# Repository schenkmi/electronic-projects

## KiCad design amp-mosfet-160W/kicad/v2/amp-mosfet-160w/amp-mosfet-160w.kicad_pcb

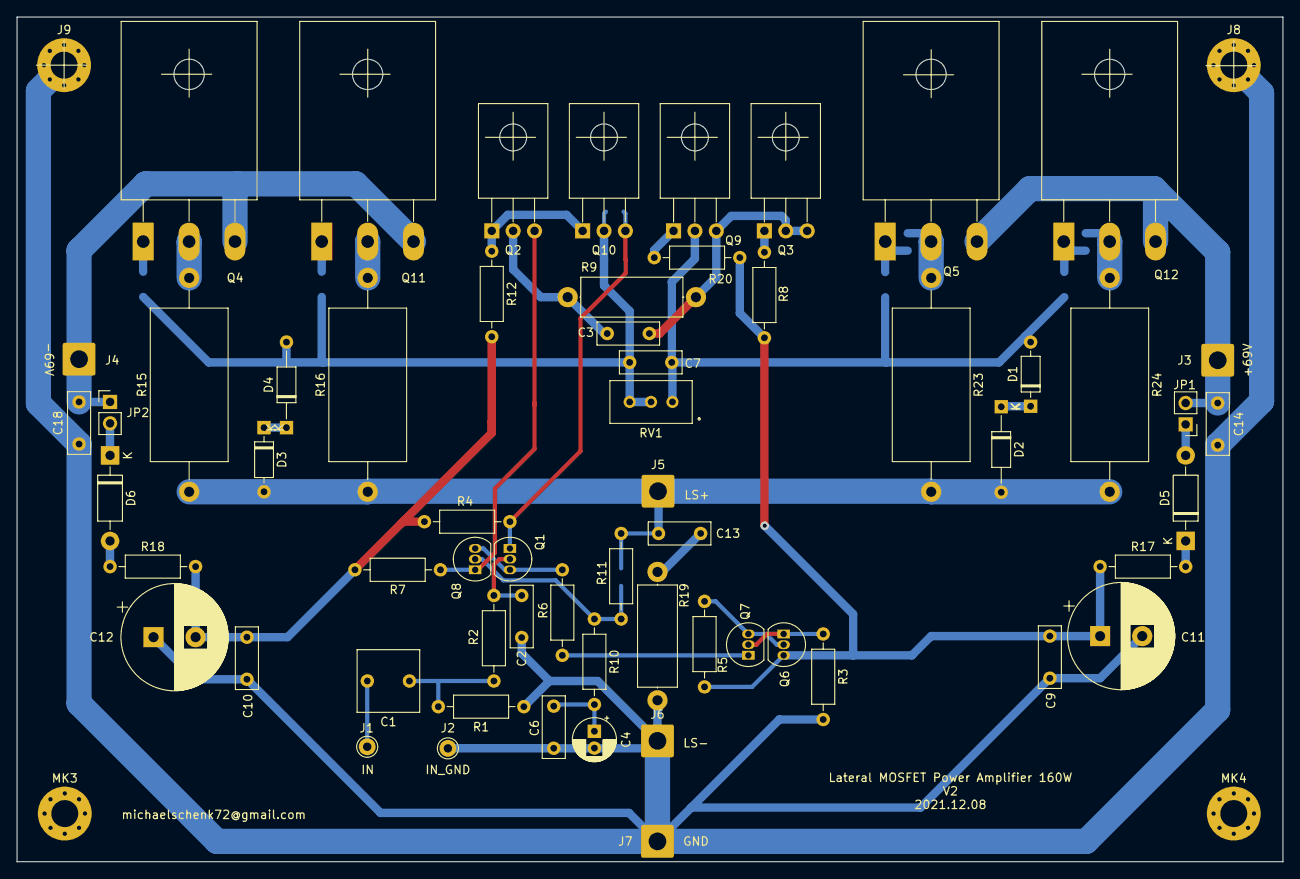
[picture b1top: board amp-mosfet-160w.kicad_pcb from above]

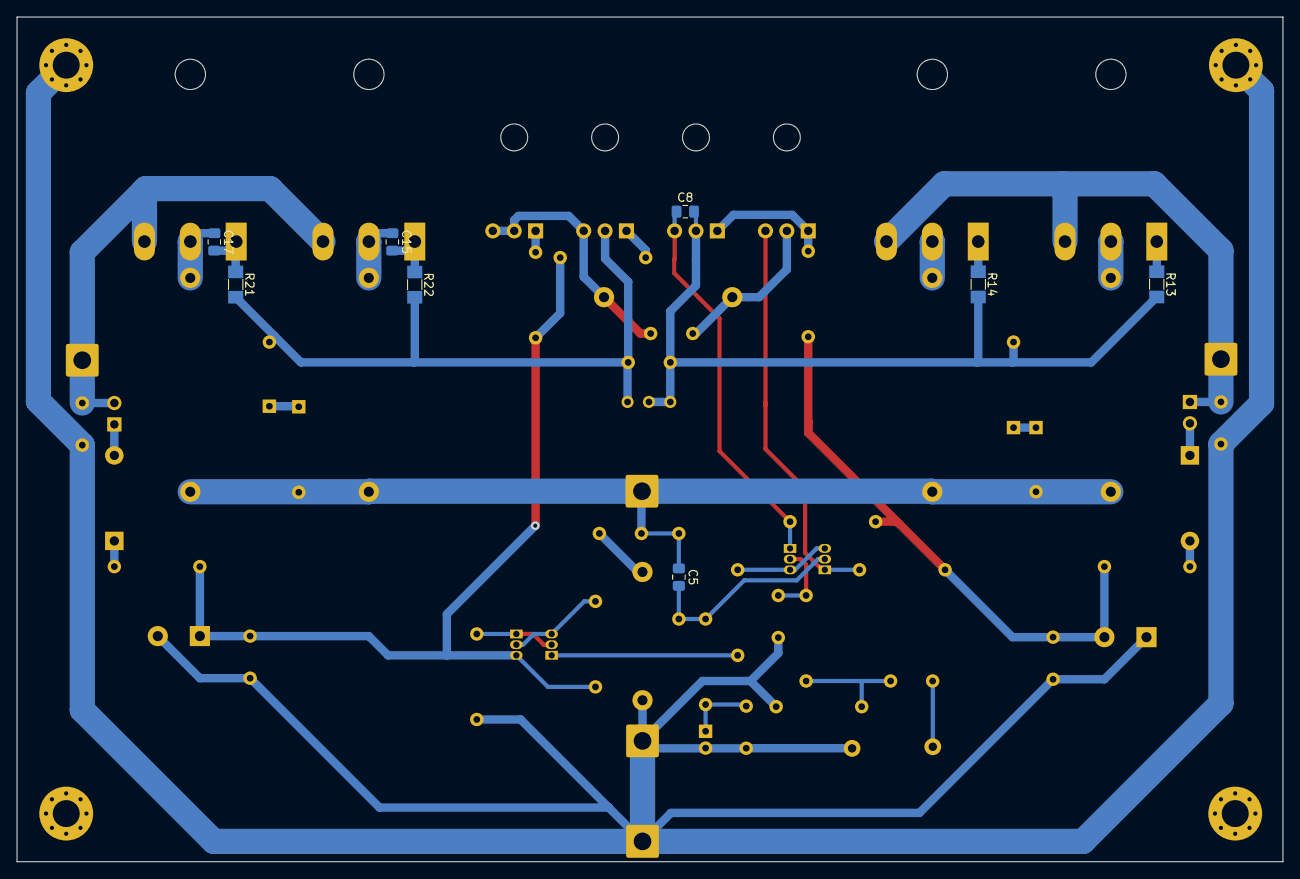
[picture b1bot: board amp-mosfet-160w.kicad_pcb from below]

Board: 2 copper layers, 150.4 x 100.3 mm, 73 parts (8 on the bottom side), 39 nets.

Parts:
C1: 2.2uF; C_Rect_L7.2mm_W7.2mm_P5.00mm_FKS2_FKP2_MKS2_MKP2
C2: 1n; C_Rect_L7.2mm_W2.5mm_P5.00mm_FKS2_FKP2_MKS2_MKP2
C3: 10n; C_Rect_L7.2mm_W2.5mm_P5.00mm_FKS2_FKP2_MKS2_MKP2
C4: 47u/16V; CP_Radial_D5.0mm_P2.00mm
C5: 10p; C_0805_2012Metric_Pad1.18x1.45mm_HandSolder
C6, C7, C9, C10, C14, C18: 100n; C_Rect_L7.2mm_W2.5mm_P5.00mm_FKS2_FKP2_MKS2_MKP2
C8: 18p; C_0805_2012Metric_Pad1.18x1.45mm_HandSolder
C11, C12: 220u/100V; CP_Radial_D12.5mm_P5.00mm
C13: 22n; C_Rect_L7.2mm_W2.5mm_P5.00mm_FKS2_FKP2_MKS2_MKP2
C15: 330p; C_0805_2012Metric_Pad1.18x1.45mm_HandSolder
C17: 470p; C_0805_2012Metric_Pad1.18x1.45mm_HandSolder
D1, D3: 1N914; D_DO-35_SOD27_P7.62mm_Horizontal
D2, D4: 12V/0.5W; D_DO-35_SOD27_P10.16mm_Horizontal
D5, D6: 1N4002; D_DO-41_SOD81_P10.16mm_Horizontal
J1, J2: Conn_01x01; Pin_D1.0mm_L10.0mm
J3: +69V; SolderWire-1.5sqmm_1x01_D1.7mm_OD3.9mm
J4: -69V; SolderWire-1.5sqmm_1x01_D1.7mm_OD3.9mm
J5: LS+; SolderWire-1.5sqmm_1x01_D1.7mm_OD3.9mm
J6: LS-; SolderWire-1.5sqmm_1x01_D1.7mm_OD3.9mm
J7: GND; SolderWire-1.5sqmm_1x01_D1.7mm_OD3.9mm
J8, J9: GND; MountingHole_3.2mm_M3_Pad_Via
JP1, JP2: Jump; PinHeader_1x02_P2.54mm_Vertical
MK3, MK4: Mounting_Hole_PAD; MountingHole_3.2mm_M3_Pad_Via
Q1, Q6, Q7, Q8: BC556; TO-92_Inline
Q2, Q10: MJE340; TO-126-3_Horizontal_TabDown
Q3, Q9: MJE350; TO-126-3_Horizontal_TabDown
Q4, Q11: ECX10P20; TO-247-3_Horizontal_TabDown
Q5, Q12: ECX10N20; TO-247-3_Horizontal_TabDown
R1, R11: 33k; R_Axial_DIN0207_L6.3mm_D2.5mm_P10.16mm_Horizontal
R2, R10: 1k; R_Axial_DIN0207_L6.3mm_D2.5mm_P10.16mm_Horizontal
R3, R6: 22k; R_Axial_DIN0207_L6.3mm_D2.5mm_P10.16mm_Horizontal
R4, R7: 4k7; R_Axial_DIN0207_L6.3mm_D2.5mm_P10.16mm_Horizontal
R5: 680R; R_Axial_DIN0207_L6.3mm_D2.5mm_P10.16mm_Horizontal
R8, R12, R17, R18, R20: 100R; R_Axial_DIN0207_L6.3mm_D2.5mm_P10.16mm_Horizontal
R9: 12k/1W; R_Axial_DIN0414_L11.9mm_D4.5mm_P15.24mm_Horizontal
R13, R14, R21, R22: 220R; R_MiniMELF_MMA-0204
R15, R16, R23, R24: 0.22R; R_Axial_DIN0918_L18.0mm_D9.0mm_P25.40mm_Horizontal
R19: 6.8R/1W; R_Axial_DIN0414_L11.9mm_D4.5mm_P15.24mm_Horizontal
RV1: 200R; Potentiometer_Bourns_3296W_Vertical

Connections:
GND: C2.2, C4.2, C6.2, C9.2, C10.1, C11.2, C12.1, C14.2, C18.1, J2.1, J6.1, J7.1, J8.1, J9.1, R1.2, R3.2, R19.2
unnamed: C1.1, R1.1, R2.2
unnamed: C1.2, J1.1
unnamed: C2.1, Q1.2, R2.1
unnamed: C3.1, Q3.2, Q3.3, Q9.3, R9.1
unnamed: C3.2, Q2.2, R9.2
unnamed: C4.1, C6.1, R10.2
unnamed: C5.2, Q8.2, R10.1, R11.2
unnamed: C7.1, C8.2, D4.2, Q10.2, R13.2, R14.2, RV1.2, RV1.3
unnamed: C7.2, D1.2, Q9.2, R21.2, R22.2, RV1.1
unnamed: C8.1, Q1.1, Q10.3, R4.1
unnamed: C10.2, C12.2, R4.2, R7.2, R12.2, R18.2
unnamed: C9.1, C11.1, Q6.3, R5.1, R8.1, R17.1, R20.1
unnamed: C5.1, C13.1, D2.2, D3.2, J5.1, R11.1, R15.1, R16.1, R23.2, R24.2
unnamed: C13.2, R19.1
unnamed: C14.1, J3.1, JP1.2, Q5.3, Q12.3
unnamed: C15.1, Q5.2, R23.1
unnamed: C15.2, Q5.1, R22.1
unnamed: C17.1, Q12.2, R24.1
unnamed: C17.2, Q12.1, R21.1
unnamed: C18.2, J4.1, JP2.1, Q4.3, Q11.3
unnamed: D1.1, D2.1
unnamed: D3.1, D4.1
unnamed: D5.1, R17.2
unnamed: D5.2, JP1.1
unnamed: D6.1, JP2.2
unnamed: D6.2, R18.1
unnamed: Q1.3, Q8.3, R6.2
unnamed: Q2.3, Q8.1, R7.1
unnamed: Q3.1, R8.2
unnamed: Q4.1, R13.1
unnamed: Q4.2, R15.2
unnamed: Q6.1, Q7.2, R3.1
unnamed: Q6.2, Q7.3, R5.2
unnamed: Q7.1, R6.1
unnamed: Q9.1, R20.2
unnamed: Q2.1, Q10.1, R12.1
unnamed: Q11.1, R14.1
unnamed: Q11.2, R16.2

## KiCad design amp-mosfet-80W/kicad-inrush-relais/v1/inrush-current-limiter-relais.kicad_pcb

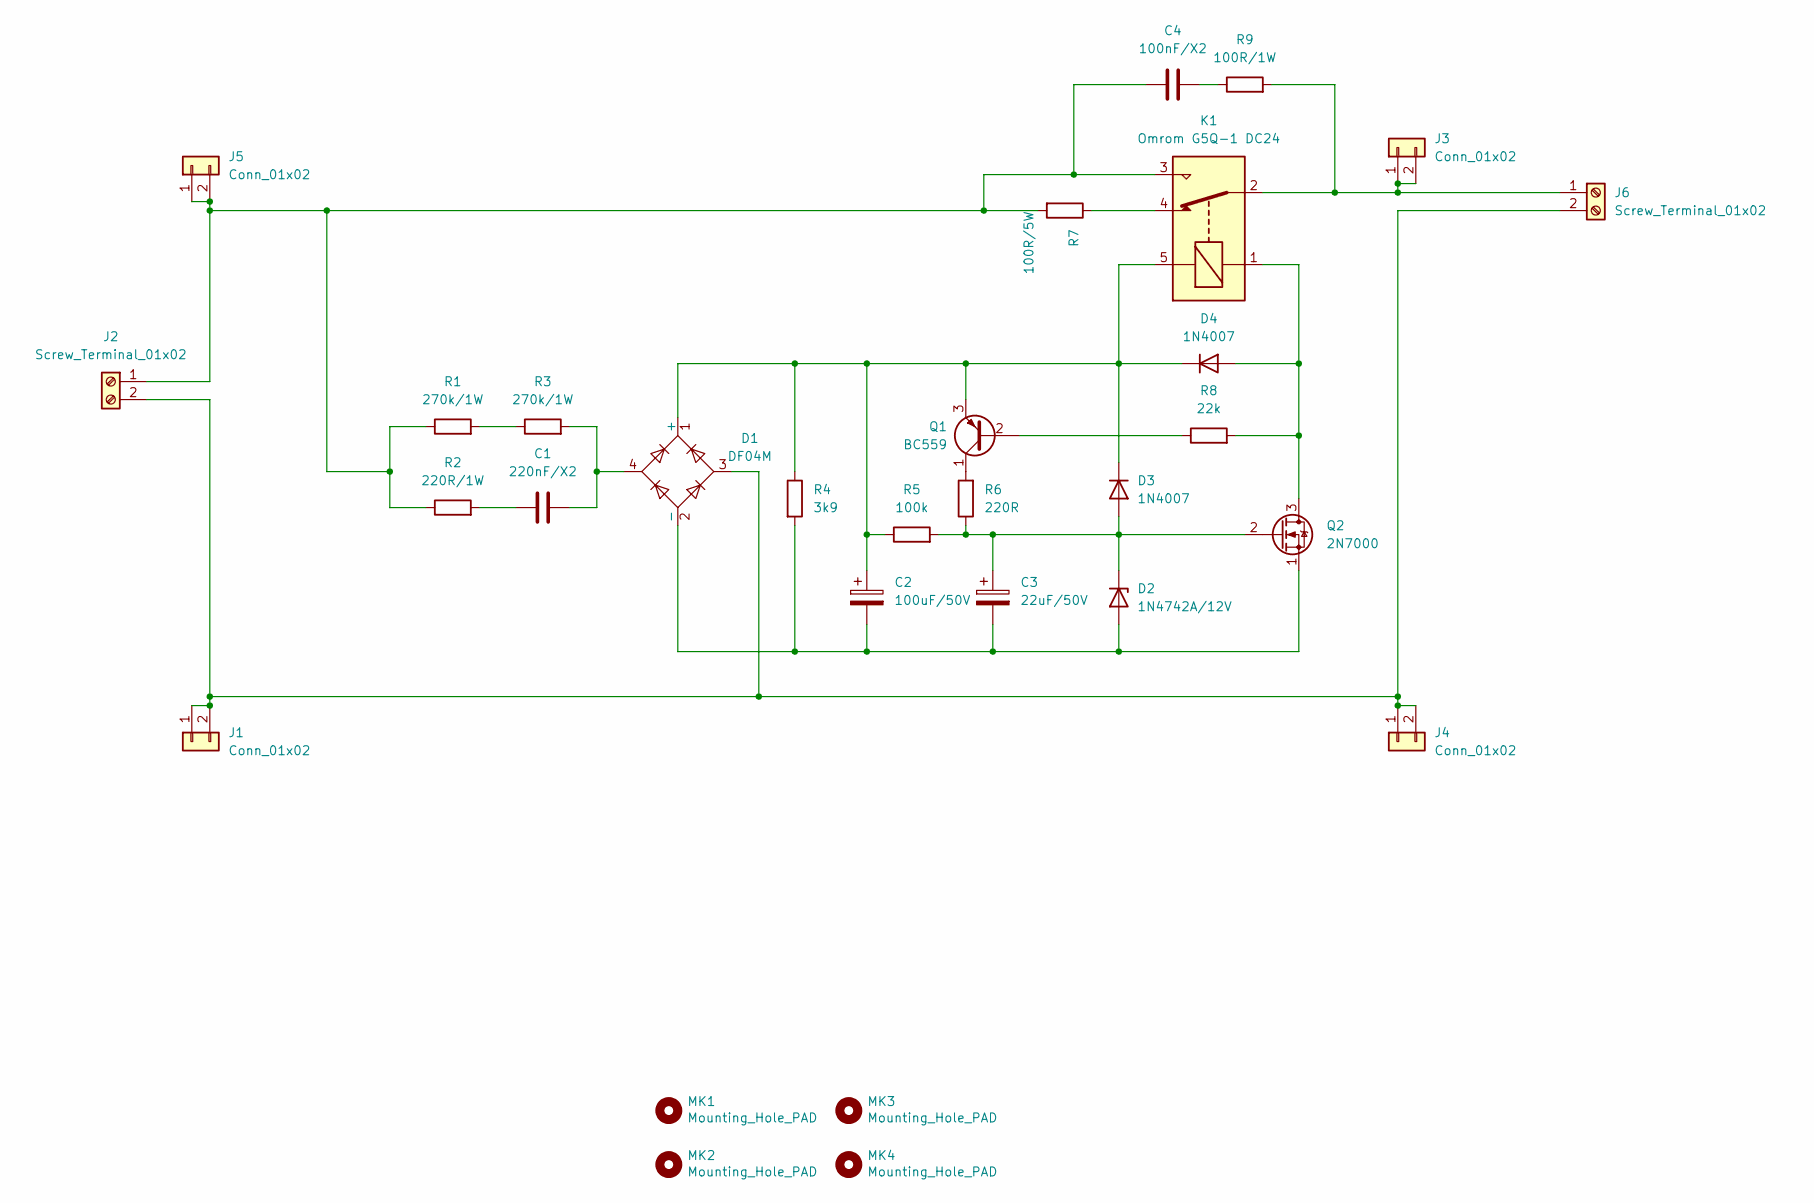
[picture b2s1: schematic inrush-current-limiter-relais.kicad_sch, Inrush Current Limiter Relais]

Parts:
C1: 220nF/X2; C_Rect_L18.0mm_W7.0mm_P15.00mm_FKS3_FKP3
C2: 100uF/50V; CP_Radial_D8.0mm_P3.50mm
C3: 22uF/50V; CP_Radial_D5.0mm_P2.00mm
C4: 100nF/X2; C_Rect_L18.0mm_W5.0mm_P15.00mm_FKS3_FKP3
D1: DF04M; Diode_Bridge_DIP-4_W7.62mm_P5.08mm
D2: 1N4742A/12V; D_DO-41_SOD81_P10.16mm_Horizontal
D3, D4: 1N4007; D_DO-41_SOD81_P10.16mm_Horizontal
J1, J3, J4, J5: Conn_01x02; TE_62409-1
J2, J6: Screw_Terminal_01x02; TerminalBlock_RND_205-00012_1x02_P5.00mm_Horizontal
K1: Omrom G5Q-1 DC24; Relay_SPDT_Omron-G5Q-1
MK1, MK2, MK3, MK4: Mounting_Hole_PAD; MountingHole_3.2mm_M3_Pad_Via
Q1: BC559; TO-92_Inline
Q2: 2N7000; TO-92_Inline
R1, R3: 270k/1W; R_Axial_DIN0207_L6.3mm_D2.5mm_P15.24mm_Horizontal
R2: 220R/1W; R_Axial_DIN0207_L6.3mm_D2.5mm_P15.24mm_Horizontal
R4: 3k9; R_Axial_DIN0207_L6.3mm_D2.5mm_P10.16mm_Horizontal
R5: 100k; R_Axial_DIN0207_L6.3mm_D2.5mm_P10.16mm_Horizontal
R6: 220R; R_Axial_DIN0207_L6.3mm_D2.5mm_P10.16mm_Horizontal
R7: 100R/5W; R_Axial_Power_L25.0mm_W9.0mm_P30.48mm
R8: 22k; R_Axial_DIN0207_L6.3mm_D2.5mm_P10.16mm_Horizontal
R9: 100R/1W; R_Axial_DIN0207_L6.3mm_D2.5mm_P15.24mm_Horizontal

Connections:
unnamed: C1.1, R2.2
unnamed: C1.2, D1.4, R3.2
unnamed: C4.2, R9.1
unnamed: C2.2, C3.2, D1.2 (-), D2.2 (A), Q2.1 (S), R4.2
unnamed: D1.3, J1.1, J1.2, J2.2, J4.1, J4.2, J6.2
unnamed: D4.2 (A), K1.1, Q2.3 (D), R8.2
unnamed: J3.1, J3.2, J6.1, K1.2, R9.2
unnamed: C4.1, J2.1, J5.1, J5.2, K1.3, R1.1, R2.1, R7.2
unnamed: K1.4, R7.1
unnamed: C2.1, D1.1 (+), D3.1 (K), D4.1 (K), K1.5, Q1.3 (E), R4.1, R5.1
unnamed: Q1.1 (C), R6.2
unnamed: Q1.2 (B), R8.1
unnamed: C3.1, D2.1 (K), D3.2 (A), Q2.2 (G), R5.2, R6.1
unnamed: R1.2, R3.1

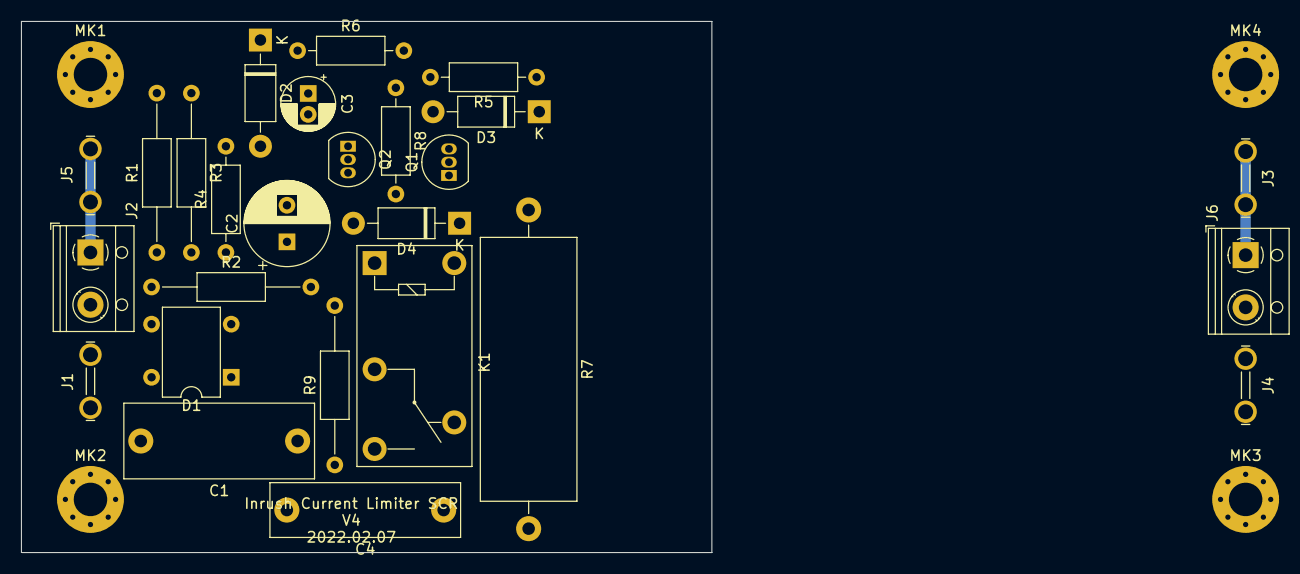
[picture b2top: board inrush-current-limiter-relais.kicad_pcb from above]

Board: 2 copper layers, 66.0 x 50.8 mm, 30 parts (0 on the bottom side), 14 nets.

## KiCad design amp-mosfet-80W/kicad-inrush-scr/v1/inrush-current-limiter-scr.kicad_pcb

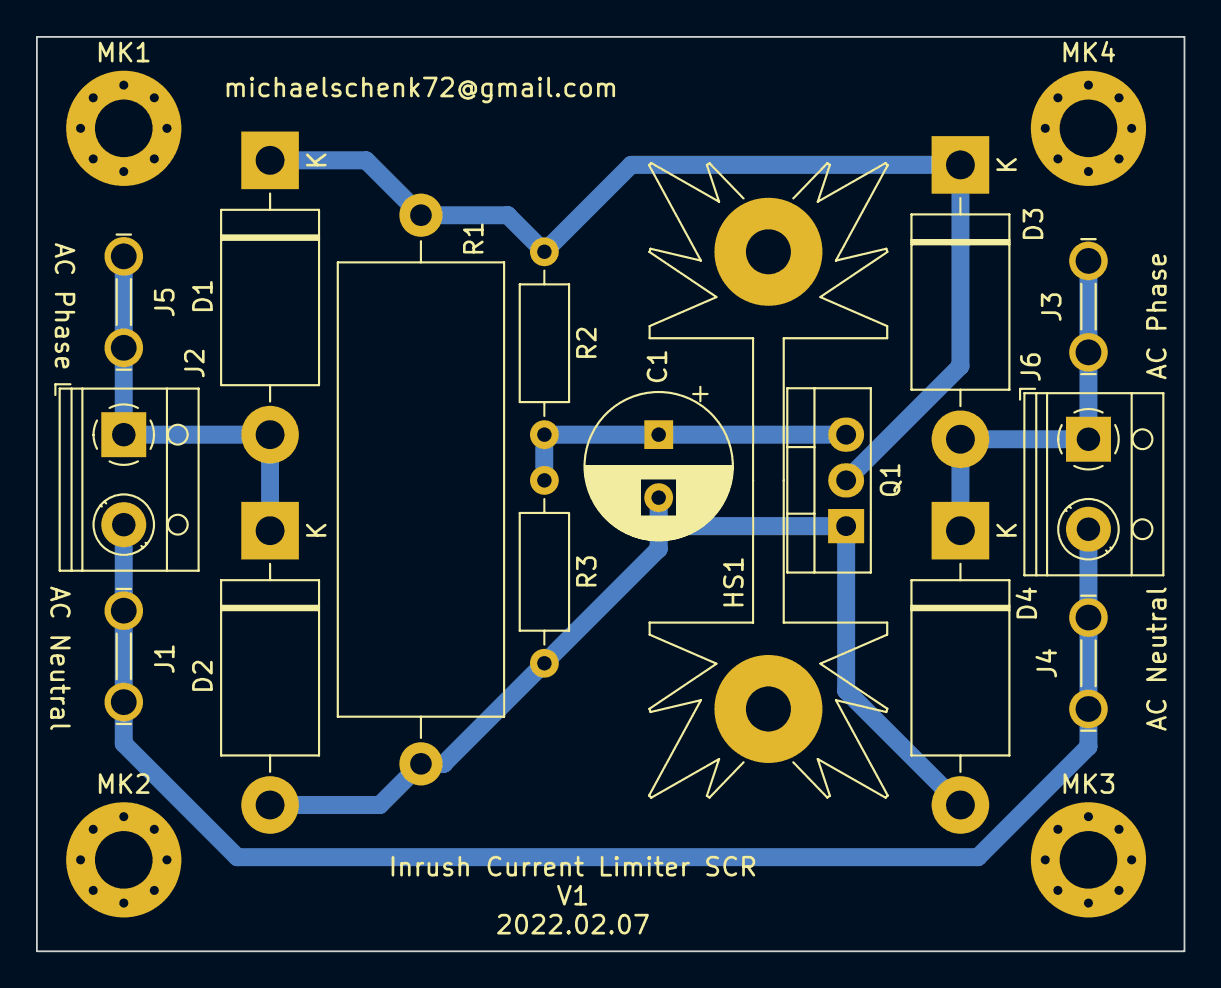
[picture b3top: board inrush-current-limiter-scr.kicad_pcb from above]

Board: 2 copper layers, 63.8 x 50.8 mm, 20 parts (0 on the bottom side), 6 nets.

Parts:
C1: 100uF/50V; CP_Radial_D8.0mm_P3.50mm
D1, D2, D3, D4: 1N5404; D_DO-201AD_P15.24mm_Horizontal
HS1: Heatsink; Heatsink_Fischer_SK104-STC-STIC_35x13mm_2xDrill2.5mm
J1, J3, J4, J5: Conn_01x02; TE_62409-1
J2, J6: Screw_Terminal_01x02; TerminalBlock_RND_205-00012_1x02_P5.00mm_Horizontal
MK1, MK2, MK3, MK4: Mounting_Hole_PAD; MountingHole_3.2mm_M3_Pad_Via
Q1: S6010RS2TP; TO-220-3_Vertical
R1: 100R; R_Axial_Power_L25.0mm_W9.0mm_P30.48mm
R2: 910k; R_Axial_DIN0207_L6.3mm_D2.5mm_P10.16mm_Horizontal
R3: 69k; R_Axial_DIN0207_L6.3mm_D2.5mm_P10.16mm_Horizontal

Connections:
unnamed: C1.1, Q1.3 (G), R2.2, R3.1
unnamed: C1.2, D2.2 (A), D4.2 (A), Q1.1 (K), R1.2, R3.2
unnamed: D1.1 (K), D3.1 (K), Q1.2 (A), R1.1, R2.1
unnamed: D1.2 (A), D2.1 (K), J2.1, J5.1, J5.2
unnamed: D3.2 (A), D4.1 (K), J3.1, J3.2, J6.1
unnamed: J1.1, J1.2, J2.2, J4.1, J4.2, J6.2

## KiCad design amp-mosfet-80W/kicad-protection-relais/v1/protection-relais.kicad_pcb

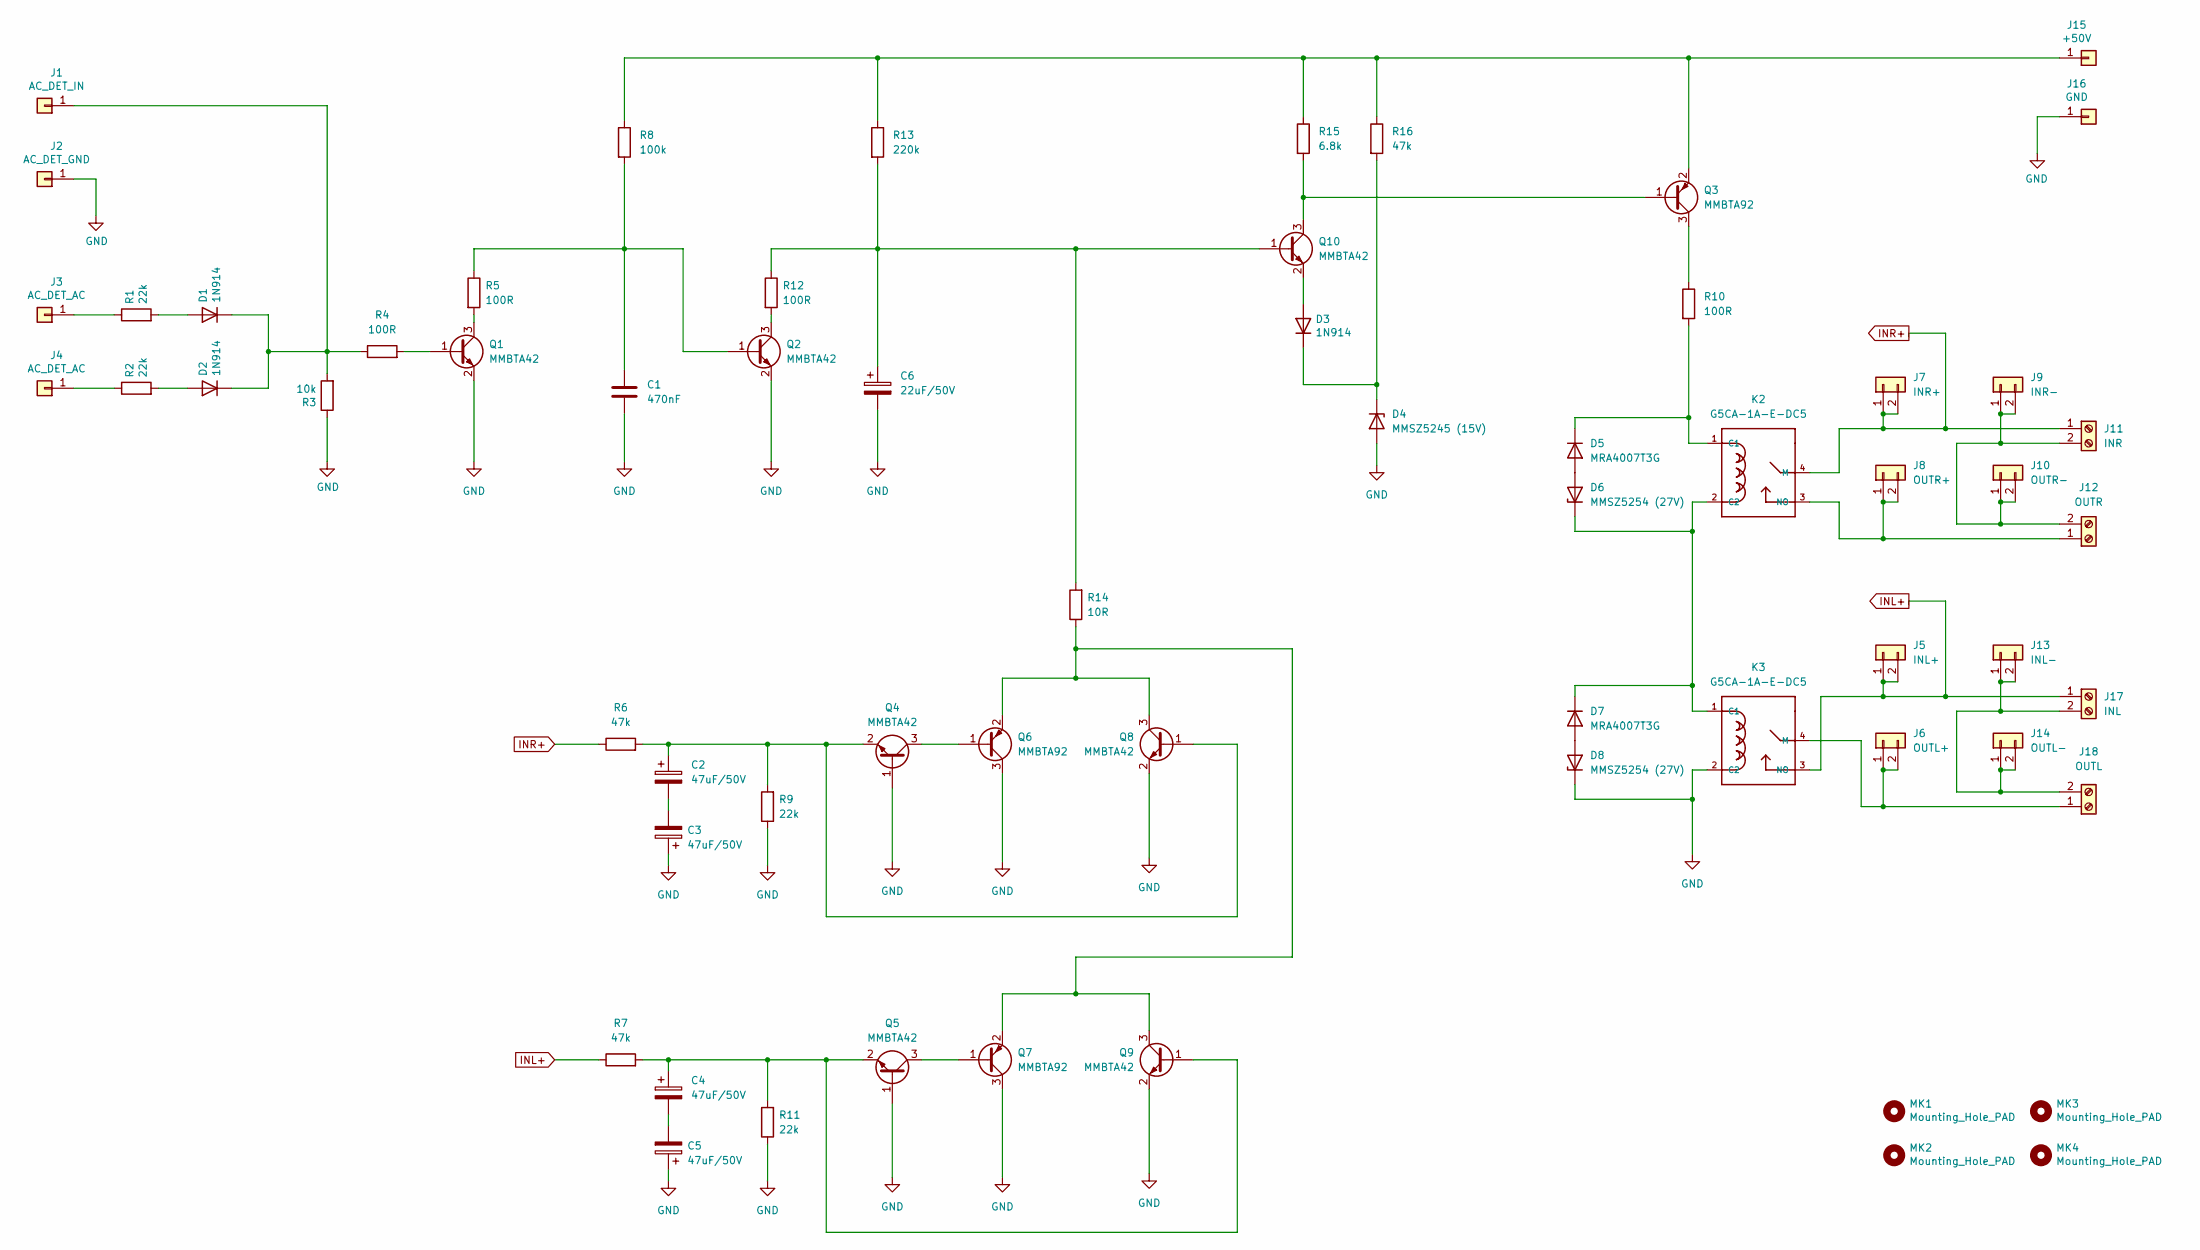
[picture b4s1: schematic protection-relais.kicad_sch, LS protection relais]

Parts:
C1: 470nF; C_1206_3216Metric_Pad1.33x1.80mm_HandSolder
C2, C3, C4, C5: 47uF/50V; CP_Radial_D6.3mm_P2.50mm
C6: 22uF/50V; CP_Radial_D5.0mm_P2.00mm
D1, D2, D3: 1N914; D_SOD-123
D4: MMSZ5245 (15V); D_SOD-123
D5, D7: MRA4007T3G; D_SMA
D6, D8: MMSZ5254 (27V); D_SOD-123
J1: AC_DET_IN; Pin_D1.0mm_L10.0mm
J2: AC_DET_GND; Pin_D1.0mm_L10.0mm
J3, J4: AC_DET_AC; Pin_D1.0mm_L10.0mm
J5: INL+; TE_62409-1
J6: OUTL+; TE_62409-1
J7: INR+; TE_62409-1
J8: OUTR+; TE_62409-1
J9: INR-; TE_62409-1
J10: OUTR-; TE_62409-1
J11: INR; TerminalBlock_RND_205-00012_1x02_P5.00mm_Horizontal
J12: OUTR; TerminalBlock_RND_205-00012_1x02_P5.00mm_Horizontal
J13: INL-; TE_62409-1
J14: OUTL-; TE_62409-1
J15: +50V; Pin_D1.0mm_L10.0mm
J16: GND; Pin_D1.0mm_L10.0mm
J17: INL; TerminalBlock_RND_205-00012_1x02_P5.00mm_Horizontal
J18: OUTL; TerminalBlock_RND_205-00012_1x02_P5.00mm_Horizontal
K2, K3: G5CA-1A-E-DC5; RELAY_G5CA-1A-E-DC5
MK1, MK2, MK3, MK4: Mounting_Hole_PAD; MountingHole_3.2mm_M3_Pad_Via
Q1, Q2, Q4, Q5, Q8, Q9, Q10: MMBTA42; SOT-23
Q3, Q6, Q7: MMBTA92; SOT-23
R1, R2, R9, R11: 22k; R_0805_2012Metric_Pad1.20x1.40mm_HandSolder
R3: 10k; R_0805_2012Metric_Pad1.20x1.40mm_HandSolder
R4, R5, R10, R12: 100R; R_0805_2012Metric_Pad1.20x1.40mm_HandSolder
R6, R7, R16: 47k; R_0805_2012Metric_Pad1.20x1.40mm_HandSolder
R8: 100k; R_0805_2012Metric_Pad1.20x1.40mm_HandSolder
R13: 220k; R_0805_2012Metric_Pad1.20x1.40mm_HandSolder
R14: 10R; R_0805_2012Metric_Pad1.20x1.40mm_HandSolder
R15: 6.8k; R_0805_2012Metric_Pad1.20x1.40mm_HandSolder

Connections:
GND: C1.2, C3.1, C5.1, C6.2, D4.2 (A), D8.1 (K), J2.1, J16.1, K3.2 (C2), Q1.2 (E), Q2.2 (E), Q4.1 (B), Q5.1 (B), Q6.3 (C), Q7.3 (C), Q8.2 (E), Q9.2 (E), R3.1, R9.1, R11.1
INL+: J5.1, J5.2, J17.1, K3.3 (NO), R7.1
INR+: J7.1, J7.2, J11.1, K2.4 (M), R6.1
unnamed: C1.1, Q2.1 (B), R5.1, R8.2
unnamed: C2.1, Q4.2 (E), Q8.1 (B), R6.2, R9.2
unnamed: C2.2, C3.2
unnamed: C4.1, Q5.2 (E), Q9.1 (B), R7.2, R11.2
unnamed: C4.2, C5.2
unnamed: C6.1, Q10.1 (B), R12.1, R13.2, R14.2
unnamed: D1.1 (K), D2.1 (K), J1.1, R3.2, R4.1
unnamed: D1.2 (A), R1.2
unnamed: D2.2 (A), R2.2
unnamed: D3.1 (K), D4.1 (K), R16.2
unnamed: D3.2 (A), Q10.2 (E)
unnamed: D5.1 (K), K2.1 (C1), R10.2
unnamed: D5.2 (A), D6.2 (A)
unnamed: D6.1 (K), D7.1 (K), K2.2 (C2), K3.1 (C1)
unnamed: D7.2 (A), D8.2 (A)
unnamed: J3.1, R1.1
unnamed: J4.1, R2.1
unnamed: J9.1, J9.2, J10.1, J10.2, J11.2, J12.2
unnamed: J8.1, J8.2, J12.1, K2.3 (NO)
unnamed: J13.1, J13.2, J14.1, J14.2, J17.2, J18.2
unnamed: J15.1, Q3.2 (E), R8.1, R13.1, R15.1, R16.1
unnamed: J6.1, J6.2, J18.1, K3.4 (M)
unnamed: Q1.1 (B), R4.2
unnamed: Q1.3 (C), R5.2
unnamed: Q2.3 (C), R12.2
unnamed: Q3.3 (C), R10.1
unnamed: Q4.3 (C), Q6.1 (B)
unnamed: Q5.3 (C), Q7.1 (B)
unnamed: Q6.2 (E), Q7.2 (E), Q8.3 (C), Q9.3 (C), R14.1
unnamed: Q3.1 (B), Q10.3 (C), R15.2

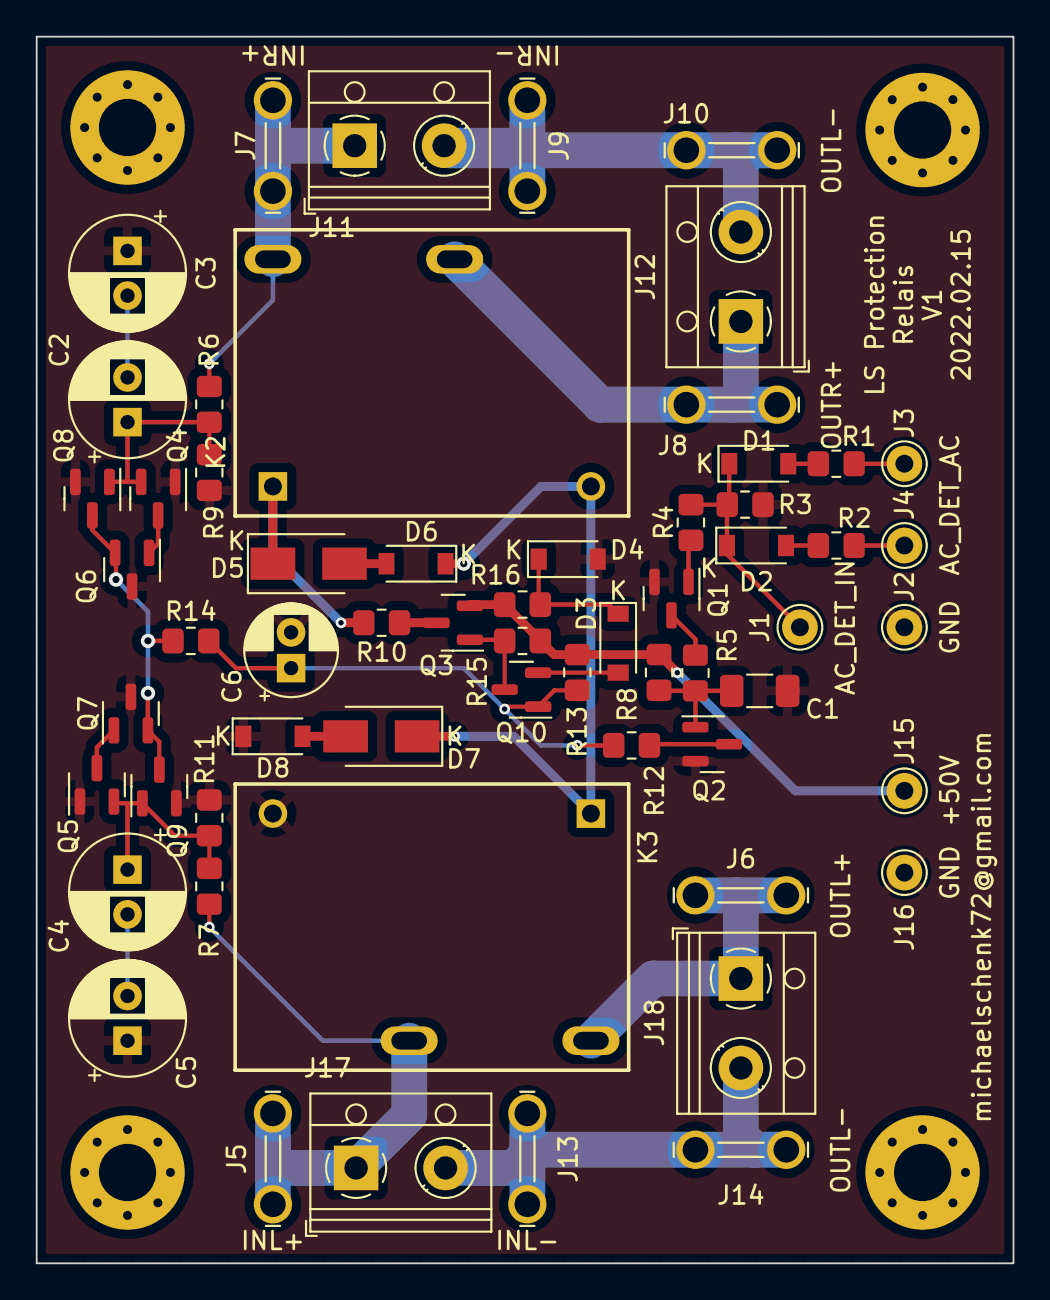
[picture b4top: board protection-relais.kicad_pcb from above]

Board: 2 copper layers, 54.6 x 68.6 mm, 64 parts (0 on the bottom side), 33 nets.
